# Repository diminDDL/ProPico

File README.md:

# ProPico
An RP2040 dev board improving on aspects of the pi pico.

### ⚠️ This project is still under development, reproduce at your own risk ⚠️
While I have assembled several of these boards and they seem to work, there is still some verification to be done, so don't expect this to be a fully finished project just yet.
## Features
- An LDO for power making the 3V3 supply much cleaner.
- Larger flash sizes up to 16MB (the higher capacities will likely require a different board revision due to the larger IC package) with binary indicators on the bottom so you remember which board has what.
- USB-C for power and programming, includes CC resistors meaning it'll work with modern USB-C chargers/cables.
- A reset button alongside the bootsel, allowing you to reboot into UF2 mode without having to unplug the board.
- Extra GPIO broken out and used:
    * GPIO 23 - connected to an extra LED.
    * GPIO 24 - connected to the EEPROM I2C line.
    * GPIO 25 - connected to the EEPROM I2C line and an LED (for compatibility with the pico led pinout).
    * GPIO 29 (ADC3) - replaces the 3V3_EN pin on the original pico, giving you an extra ADC pin.
- LM4040 voltage reference for the ADC.
- I2C EEPROM/FRAM onboard so you have easy to use non volatile storage.
- RUN pin exposed next to the debug port.

## Pinout

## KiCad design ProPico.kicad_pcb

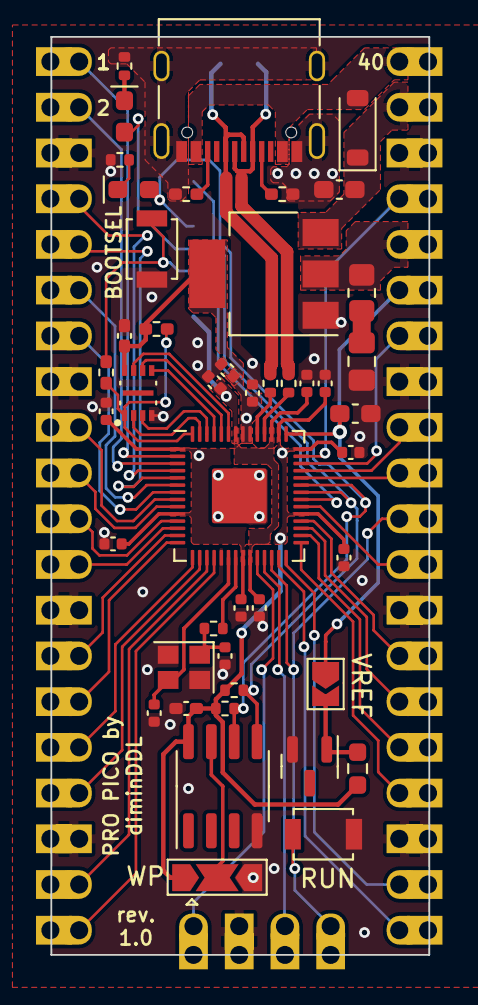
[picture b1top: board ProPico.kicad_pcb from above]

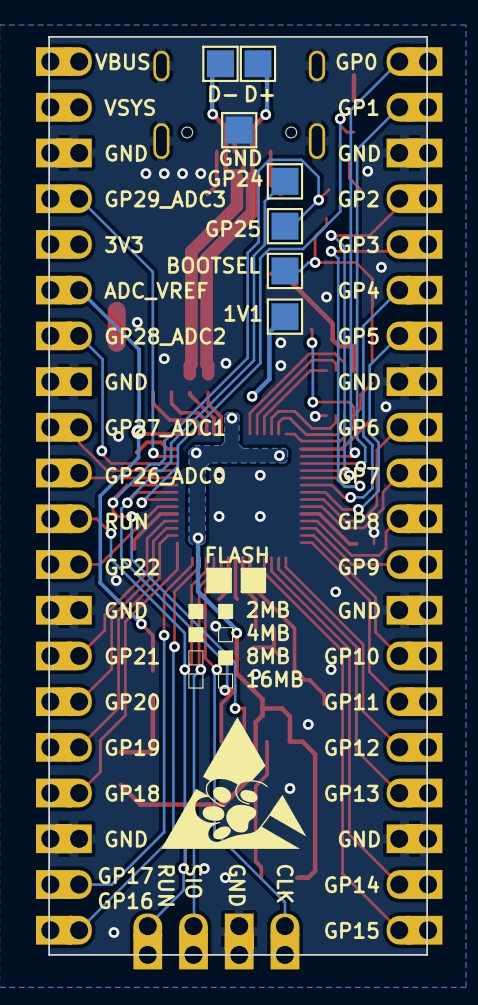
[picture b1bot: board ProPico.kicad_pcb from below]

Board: 2 copper layers, 21.0 x 51.0 mm, 55 parts (7 on the bottom side), 60 nets.

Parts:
C1, C5: 100n; C_0402_1005Metric_Pad0.74x0.62mm_HandSolder
C2, C3: 18p; C_0402_1005Metric
C4: 2.2u; C_0603_1608Metric_Pad1.08x0.95mm_HandSolder
C6: 10u; C_0805_2012Metric_Pad1.18x1.45mm_HandSolder
C7: 10n C0G; C_0603_1608Metric_Pad1.08x0.95mm_HandSolder
C8, C9, C11, C13, C14, C15, C16, C17, C18: 100n; C_0402_1005Metric
C10, C12: 1u; C_0402_1005Metric
D1: B5819W; D_SOD-123
D2, D3: LED; LED_0603_1608Metric_Pad1.05x0.95mm_HandSolder
J1: USB_C_Receptacle_USB2.0; USB_C_Receptacle_Palconn_UTC16-G
J2: SWD; Pico_4pin
J3: LEFT; Pico_20pin
J4: RIGHT; Pico_20pin
JP1: EEPROM_WP; SolderJumper-3_P2.0mm_Open_TrianglePad1.0x1.5mm
JP2: VREF; SolderJumper-2_P1.3mm_Open_TrianglePad1.0x1.5mm
R1: 1k; R_0402_1005Metric_Pad0.72x0.64mm_HandSolder
R2: DNP; R_0402_1005Metric_Pad0.72x0.64mm_HandSolder
R3, R4: 5.1k; R_0402_1005Metric_Pad0.72x0.64mm_HandSolder
R5, R10, R11, R12, R13: 1k; R_0402_1005Metric
R6: 470mOhm; R_0805_2012Metric_Pad1.20x1.40mm_HandSolder
R7: 150; R_0603_1608Metric_Pad0.98x0.95mm_HandSolder
R8, R9: 27; R_0402_1005Metric
SW1: BOOTSEL; SW_SPST_B3U-1000P
SW2: RES; SW_SPST_B3U-1000P
TP1: BOOTSEL; TestPoint_Pad_1.5x1.5mm
TP2: VREG; TestPoint_Pad_1.5x1.5mm
TP3: GP25; TestPoint_Pad_1.5x1.5mm
TP4: GND; TestPoint_Pad_1.5x1.5mm
TP5: D+; TestPoint_Pad_1.5x1.5mm
TP6: GP24; TestPoint_Pad_1.5x1.5mm
TP7: D-; TestPoint_Pad_1.5x1.5mm
U1: FM24CL16B; SOIC-8_3.9x4.9mm_P1.27mm
U2: W25Q16JVUXIQ; IC_W25Q16JVUXIQ_TR
U3: AMS1117-3.3; SOT-223-3_TabPin2
U4: LM4040DBZ-3; SOT-23
U5: RP2040; RP2040-QFN-56
Y1: ECS-120-12-36-AGN-TR3; Crystal_SMD_2520-4Pin_2.5x2.0mm

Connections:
+1V1: C8.1, C9.1, C10.1, TP2.1, U5.23 (DVDD), U5.45 (VREG_VOUT), U5.50 (DVDD)
+3V3: C1.1, C5.1, C11.1, C12.1, C13.1, C14.1, C15.1, C16.1, C17.1, C18.1, J4.16, JP1.1 (A), R2.1, R6.2, R7.2, R10.1, R11.1, U1.8 (VDD), U2.8 (VCC), U3.2 (VO), U5.1 (IOVDD), U5.10 (IOVDD), U5.22 (IOVDD), U5.33 (IOVDD), U5.42 (IOVDD), U5.44 (VREG_IN), U5.48 (USB_VDD), U5.49 (IOVDD)
+5V: C4.1, D1.1 (K), J4.19, U3.3 (VI)
/3V0_VREF: JP2.2 (B), R7.1, U4.1 (K)
/ADC_VREF: C7.1, J4.15, JP2.1 (A), U5.43 (ADC_AVDD)
/D+: J1.A6 (D+), J1.B6 (D+), R8.1, TP5.1
/D-: J1.A7 (D-), J1.B7 (D-), R9.1, TP7.1
/DN: R9.2, U5.46 (USB_DM)
/DP: R8.2, U5.47 (USB_DP)
/EEPROM_SCL: D3.2 (A), R11.2, TP3.1, U1.6 (SCL), U5.37 (GPIO25)
/EEPROM_SDA: R10.2, TP6.1, U1.5 (SDA), U5.36 (GPIO24)
/EEPROM_WP: JP1.2 (C), U1.7 (WP)
/GPIO0: J3.1, U5.2 (GPIO0)
/GPIO1: J3.2, U5.3 (GPIO1)
/GPIO2: J3.4, U5.4 (GPIO2)
/GPIO3: J3.5, U5.5 (GPIO3)
/GPIO4: J3.6, U5.6 (GPIO4)
/GPIO5: J3.7, U5.7 (GPIO5)
/GPIO6: J3.9, U5.8 (GPIO6)
/GPIO7: J3.10, U5.9 (GPIO7)
/GPIO8: J3.11, U5.11 (GPIO8)
/GPIO9: J3.12, U5.12 (GPIO9)
/GPIO10: J3.14, U5.13 (GPIO10)
/GPIO11: J3.15, U5.14 (GPIO11)
/GPIO12: J3.16, U5.15 (GPIO12)
/GPIO13: J3.17, U5.16 (GPIO13)
/GPIO14: J3.19, U5.17 (GPIO14)
/GPIO15: J3.20, U5.18 (GPIO15)
/GPIO16: J4.1, U5.27 (GPIO16)
/GPIO17: J4.2, U5.28 (GPIO17)
/GPIO18: J4.4, U5.29 (GPIO18)
/GPIO19: J4.5, U5.30 (GPIO19)
/GPIO20: J4.6, U5.31 (GPIO20)
/GPIO21: J4.7, U5.32 (GPIO21)
/GPIO22: J4.9, U5.34 (GPIO22)
/GPIO23: D2.2 (A), U5.35 (GPIO23)
/GPIO26_ADC0: J4.11, U5.38 (GPIO26_ADC0)
/GPIO27_ADC1: J4.12, U5.39 (GPIO27_ADC1)
/GPIO28_ADC2: J4.14, U5.40 (GPIO28_ADC2)
/GPIO29_ADC3: J4.17, U5.41 (GPIO29_ADC3)
/QSPI_SCLK: U2.6 (CLK), U5.52 (QSPI_SCLK)
/QSPI_SD0: U2.5 (DI(IO0)), U5.53 (QSPI_SD0)
/QSPI_SD1: U2.2 (DO(IO1)), U5.55 (QSPI_SD1)
/QSPI_SD2: U2.3 (IO2), U5.54 (QSPI_SD2)
/QSPI_SD3: U2.7 (IO3), U5.51 (QSPI_SD3)
/QSPI_SS: R1.1, R2.2, U2.1 (~CS), U5.56 (QSPI_SS)
/RUN: J2.4, J4.10, SW2.1, U5.26 (RUN)
/SWCLK: J2.1, U5.24 (SWCLK)
/SWD: J2.3, U5.25 (SWD)
/XIN: C2.1, U5.20 (XIN), Y1.3
/XOUT: R5.1, U5.21 (XOUT)
GND: C1.2, C2.2, C3.2, C4.2, C5.2, C6.2, C7.2, C8.2, C9.2, C10.2, C11.2, C12.2, C13.2, C14.2, C15.2, C16.2, C17.2, C18.2, J1.A1 (GND), J1.A12 (GND), J1.B1 (GND), J1.B12 (GND), J1.S1 (SHIELD), J2.2, J3.3, J3.8, J3.13, J3.18, J4.3, J4.8, J4.13, J4.18, JP1.3 (B), R3.2, R4.2, R12.2, R13.2, SW1.1, SW2.2, TP4.1, U1.4 (VSS), U2.4 (GND), U3.1 (GND), U4.2 (A), U5.19 (TESTEN), U5.57 (GND), Y1.2, Y1.4
unnamed: C3.1, R5.2, Y1.1
unnamed: C6.1, R6.1
unnamed: D2.1 (K), R12.1
unnamed: D3.1 (K), R13.1
unnamed: J1.A5 (CC1), R4.1
unnamed: J1.B5 (CC2), R3.1
unnamed: R1.2, SW1.2, TP1.1
VBUS: D1.2 (A), J1.A4 (VBUS), J1.A9 (VBUS), J1.B4 (VBUS), J1.B9 (VBUS), J4.20

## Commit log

2022-12-28 starting the schematic
2023-10-29 started layout
2023-11-01 progress on layout
2023-11-03 finished layout
2023-11-03 finished erc
2023-11-04 finished silkscreen
2023-11-04 added render, fixed spelling mistake
2023-11-18 fixed weird filename
2023-11-24 added BOM
2023-12-12 working on svg of the pinout
2023-12-13 updated pinout
2023-12-13 finieshed pinout
2023-12-22 updated schematic
2023-12-22 made schematic less cringe
2024-02-10 wip adding part numbers to components
2024-02-10 added part numbers to everything in the schematic
2024-02-16 changed the names of some nets to be more logical
2024-02-17 added basic software template
